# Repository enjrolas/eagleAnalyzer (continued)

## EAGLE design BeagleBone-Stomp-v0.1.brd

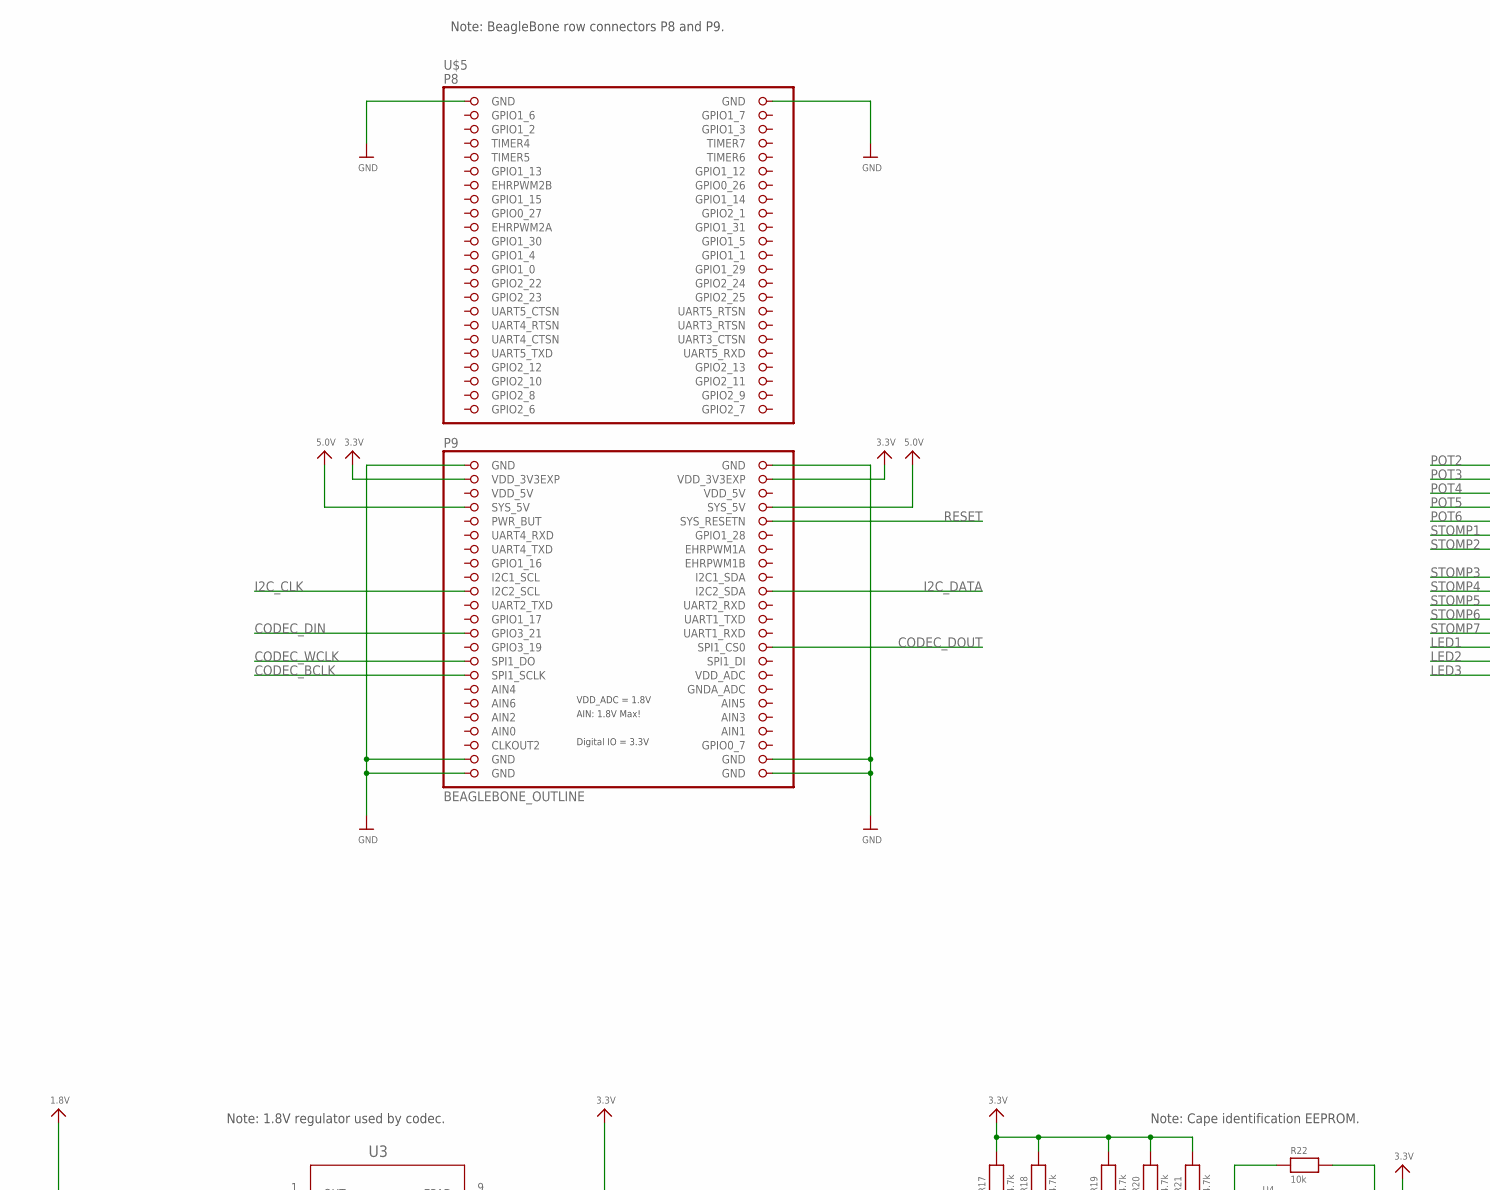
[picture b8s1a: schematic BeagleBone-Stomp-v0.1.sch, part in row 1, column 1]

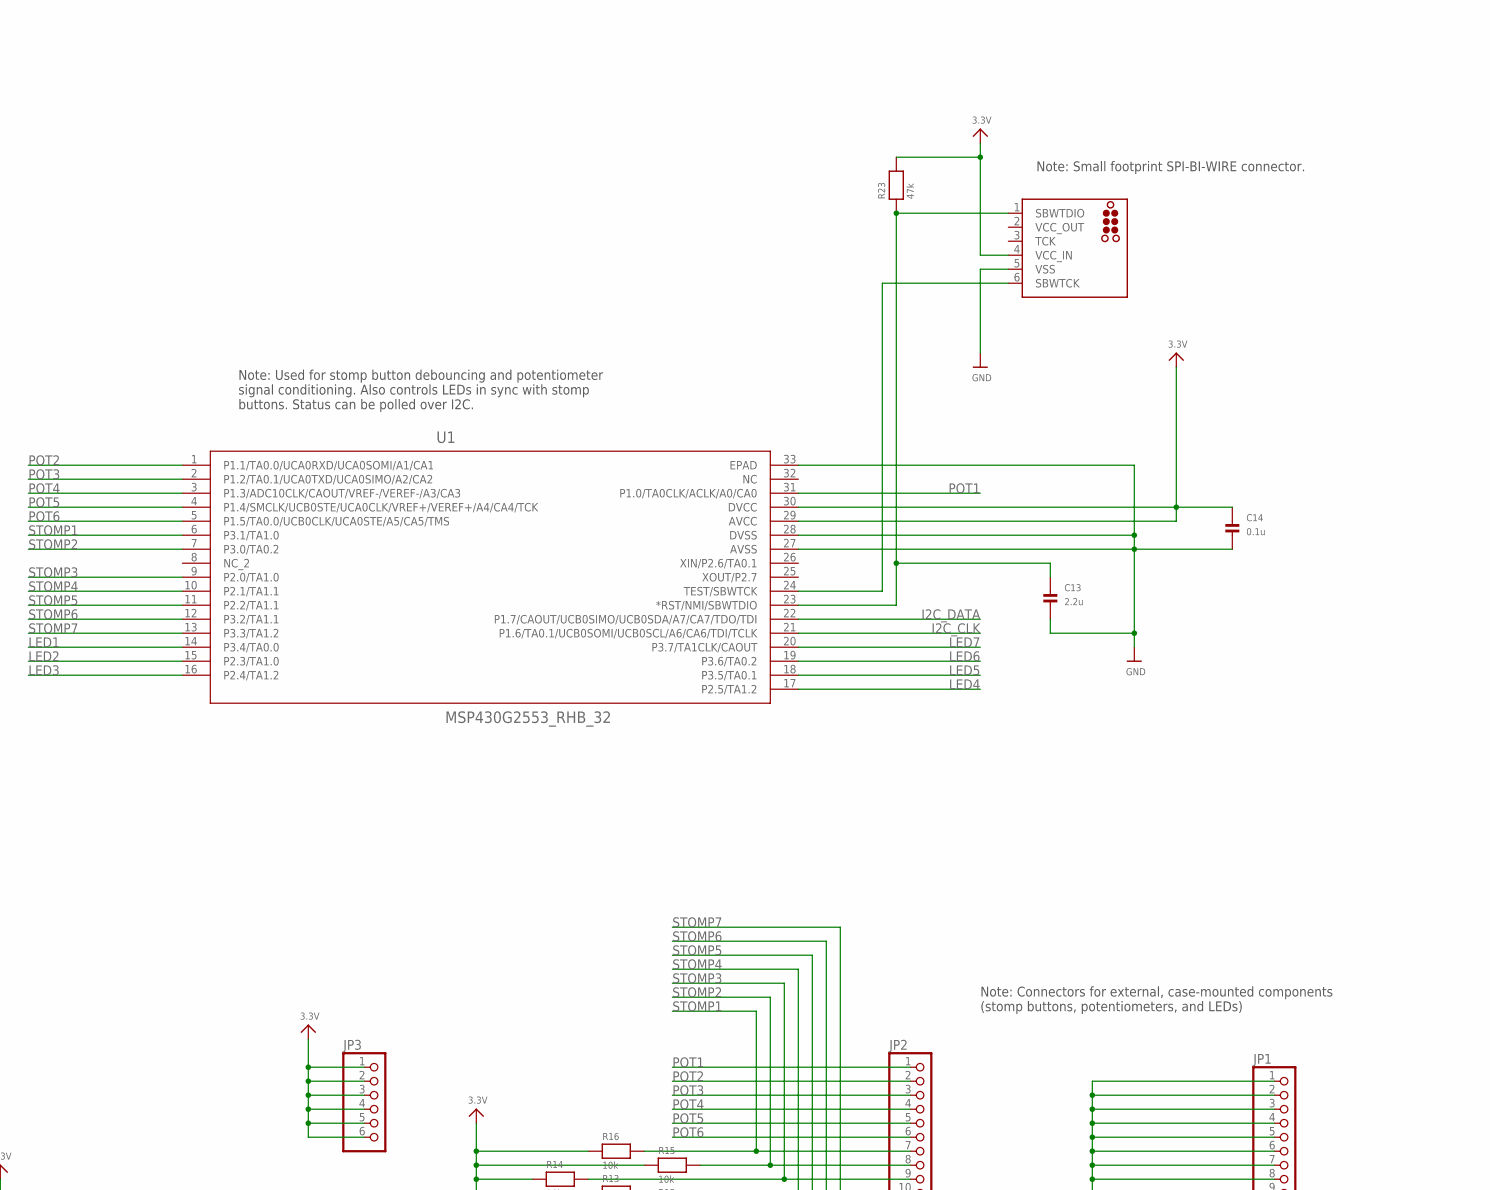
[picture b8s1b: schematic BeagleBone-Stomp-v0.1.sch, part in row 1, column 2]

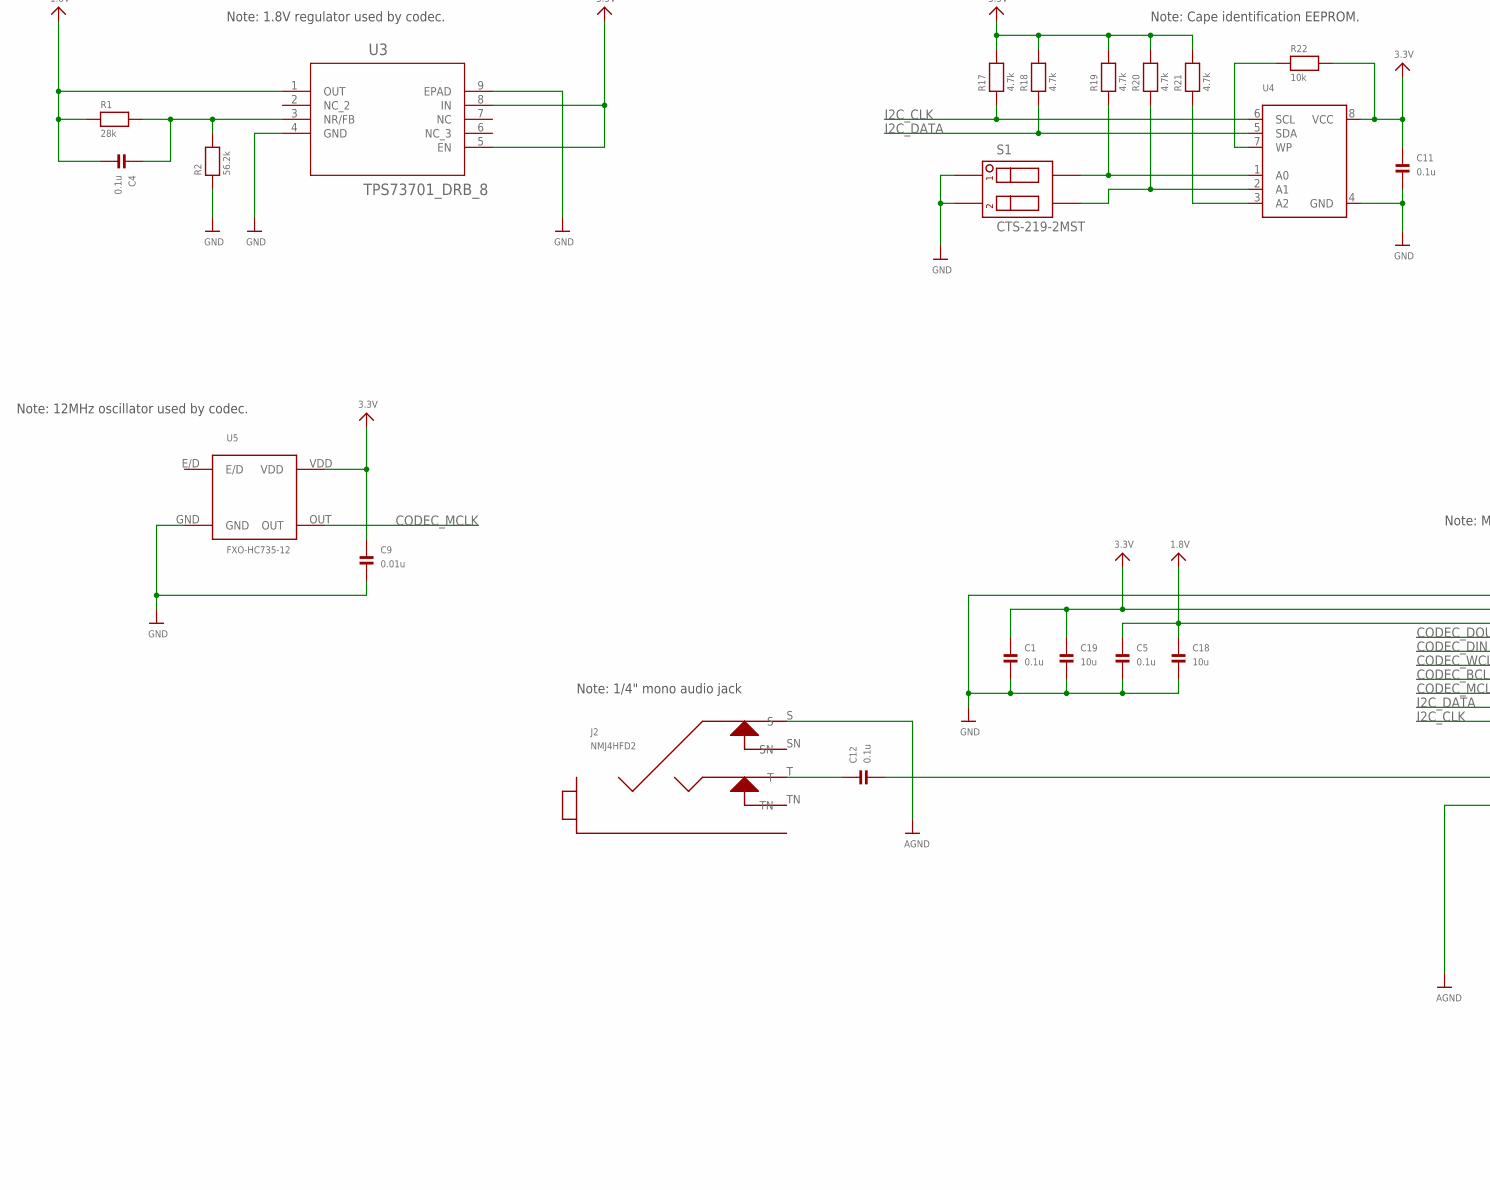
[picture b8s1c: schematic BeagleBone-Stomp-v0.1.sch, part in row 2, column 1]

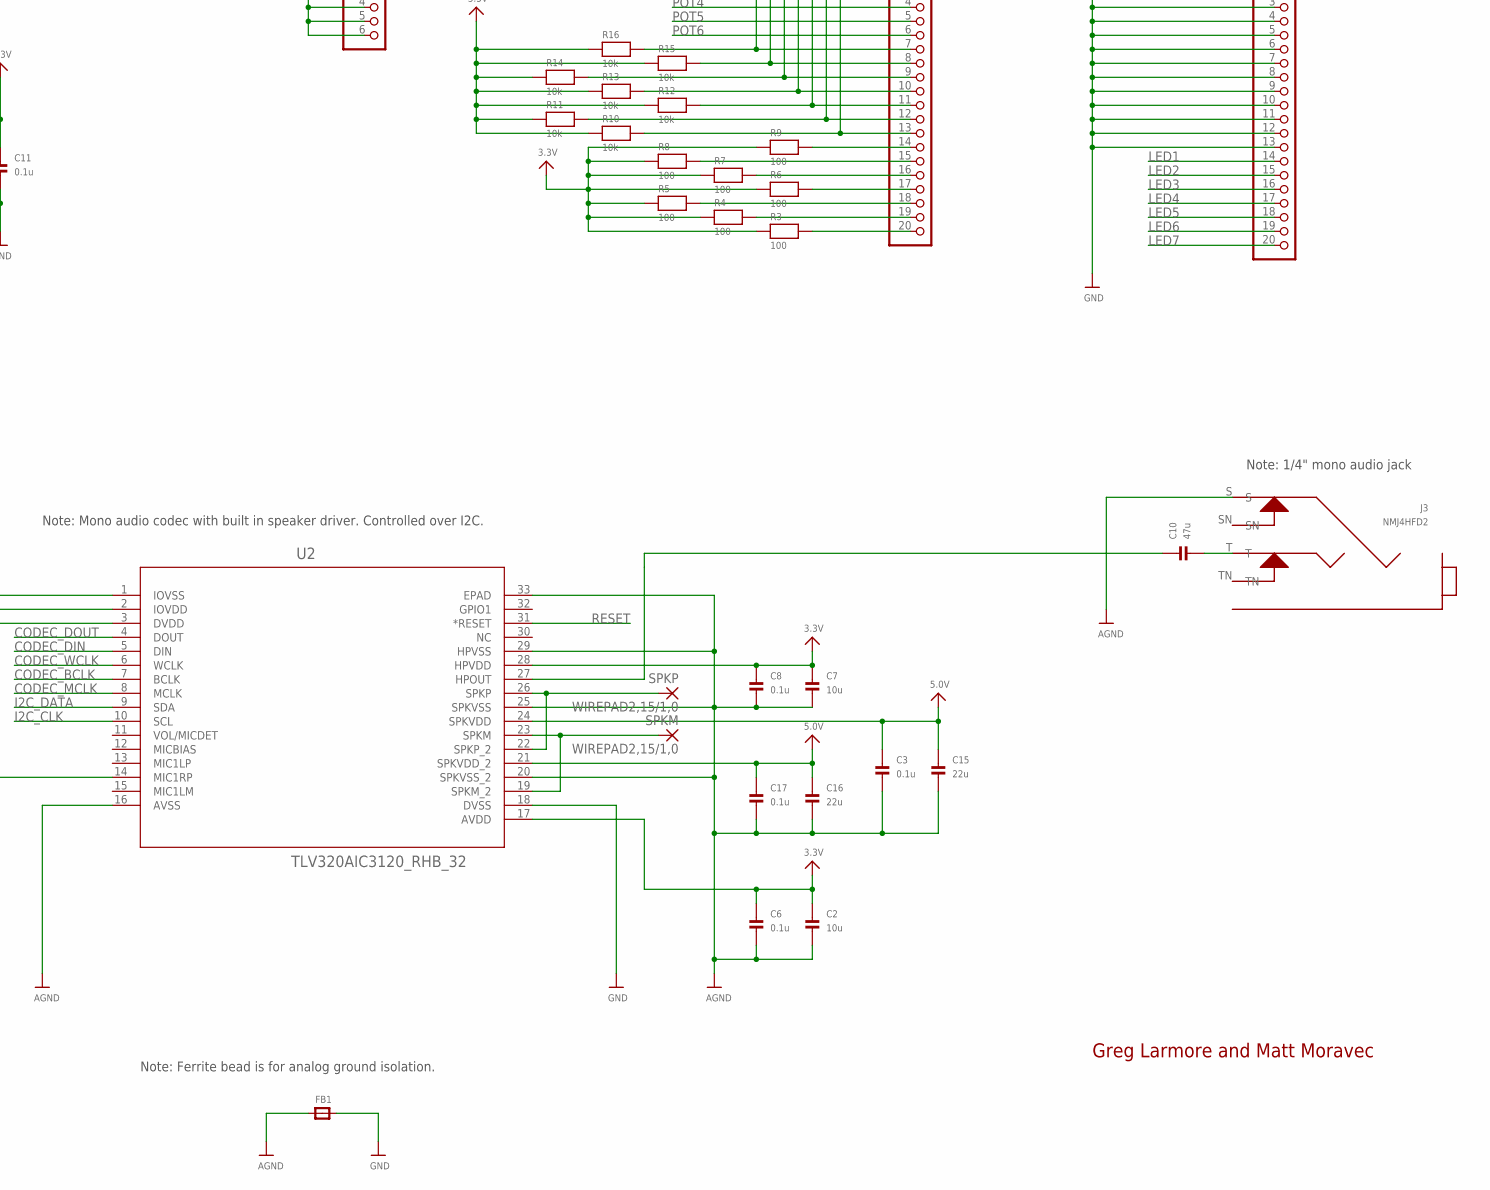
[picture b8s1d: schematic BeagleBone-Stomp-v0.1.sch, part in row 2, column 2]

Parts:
C1, C3, C4, C5, C6, C8, C11, C12, C14, C17: 0.1u; 0402
C2, C7, C18, C19: 10u; 0805
C9: 0.01u; 0402
C10: 47u; 0805
C13: 2.2u; 0402
C15, C16: 22u; 0805
FB1: FERRITE_0402; _0402
J1: TC2030-MCP
J2, J3: NMJ4HFD2
JP1, JP2: HEADER-1X20ROUND; 1X20_ROUND
JP3: HEADER-1X6ROUND; 1X06_ROUND
R1: 28k; 0402
R2: 56.2k; 0402
R3, R4, R5, R6, R7, R8, R9: 100; 0402
R10, R11, R12, R13, R14, R15, R16, R22: 10k; 0402
R17, R18, R19, R20, R21: 4.7k; 0402
R23: 47k; 0402
S1: CTS-219-2MST
SPKM: WIREPAD2,15/1,0; 2,15/1,0
SPKP: WIREPAD2,15/1,0; 2,15/1,0
U1: MSP430G2553_RHB_32; RHB32_3P45X3P45
U2: TLV320AIC3120_RHB_32; RHB32_3P45X3P45
U3: TPS73701_DRB_8; DRB8_1P75X1P5
U4: EEPROM_I2C_SOIC8_GENERIC; SOIC8_150MIL
U5: FXO-HC735-12
U$5: BEAGLEBONE_OUTLINE; BEAGLEBONE_SHIELD

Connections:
1.8V: C4.2, C5.1, C18.1, R1.1, U2.3 (DVDD), U3.1 (OUT)
3.3V: C1.1, C2.1, C6.1, C7.1, C8.1, C9.1, C11.1, C14.1, C19.1, J1.4 (VCC_IN), JP3.1, JP3.2, JP3.3, JP3.4, JP3.5, JP3.6, R3.1, R4.1, R5.1, R6.1, R7.1, R8.1, R9.1, R10.1, R11.1, R12.1, R13.1, R14.1, R15.1, R16.1, R17.2, R18.2, R19.2, R20.2, R21.2, R22.2, R23.2, U1.29 (AVCC), U1.30 (DVCC), U2.2 (IOVDD), U2.17 (AVDD), U2.28 (HPVDD), U3.5 (EN), U3.8 (IN), U4.8 (VCC), U5.VDD, U$5.49 (VDD_3V3EXP), U$5.50 (VDD_3V3EXP)
5.0V: C3.1, C15.1, C16.1, C17.1, U2.21 (SPKVDD_2), U2.24 (SPKVDD), U$5.53 (SYS_5V), U$5.54 (SYS_5V)
AGND: C2.2, C3.2, C6.2, C7.2, C8.2, C15.2, C16.2, C17.2, FB1.1, J2.S, J3.S, U2.16 (AVSS), U2.20 (SPKVSS_2), U2.25 (SPKVSS), U2.29 (HPVSS), U2.33 (EPAD)
CODEC_BCLK: U2.7 (BCLK), U$5.77 (SPI1_SCLK)
CODEC_DIN: U2.5 (DIN), U$5.71 (GPIO3_21)
CODEC_DOUT: U2.4 (DOUT), U$5.74 (SPI1_CS0)
CODEC_MCLK: U2.8 (MCLK), U5.OUT
CODEC_WCLK: U2.6 (WCLK), U$5.75 (SPI1_DO)
GND: C1.2, C5.2, C9.2, C11.2, C13.2, C14.2, C18.2, C19.2, FB1.2, J1.5 (VSS), JP1.1, JP1.2, JP1.3, JP1.4, JP1.5, JP1.6, JP1.7, JP1.8, JP1.9, JP1.10, JP1.11, JP1.12, JP1.13, R2.1, S1.P$1, S1.P$2, U1.27 (AVSS), U1.28 (DVSS), U1.33 (EPAD), U2.1 (IOVSS), U2.18 (DVSS), U3.4 (GND), U3.9 (EPAD), U4.4 (GND), U5.GND, U$5.1 (GND), U$5.2 (GND), U$5.47 (GND), U$5.48 (GND), U$5.89 (GND), U$5.90 (GND), U$5.91 (GND), U$5.92 (GND)
GNDA_ADC: U$5.80 (GNDA_ADC)
I2C_CLK: R17.1, U1.21 (P1.6/TA0.1/UCB0SOMI/UCB0SCL/A6/CA6/TDI/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), U2.10 (SCL), U4.6 (SCL), U$5.65 (I2C2_SCL)
I2C_DATA: R18.1, U1.22 (P1.7/CAOUT/UCB0SIMO/UCB0SDA/A7/CA7/TDO/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), U2.9 (SDA), U4.5 (SDA), U$5.66 (I2C2_SDA)
LED1: JP1.14, U1.14 (P3.4/TA0.0)
LED2: JP1.15, U1.15 (P2.3/TA1.0)
LED3: JP1.16, U1.16 (P2.4/TA1.2)
LED4: JP1.17, U1.17 (P2.5/TA1.2)
LED5: JP1.18, U1.18 (P3.5/TA0.1)
LED6: JP1.19, U1.19 (P3.6/TA0.2)
LED7: JP1.20, U1.20 (P3.7/TA1CLK/CAOUT)
unnamed: C4.1, R1.2, R2.2, U3.3 (NR/FB)
unnamed: SPKM.1, U2.19 (SPKM_2), U2.23 (SPKM)
unnamed: SPKP.1, U2.22 (SPKP_2), U2.26 (SPKP)
unnamed: R19.1, S1.P$4, U4.1 (A0)
unnamed: C10.2, J3.T
unnamed: JP2.20, R3.2
unnamed: C10.1, U2.27 (HPOUT)
unnamed: C12.1, J2.T
unnamed: C12.2, U2.14 (MIC1RP)
unnamed: R20.1, S1.P$3, U4.2 (A1)
unnamed: R21.1, U4.3 (A2)
unnamed: JP2.14, R9.2
unnamed: JP2.15, R8.2
unnamed: JP2.16, R7.2
unnamed: JP2.17, R6.2
unnamed: R22.1, U4.7 (WP)
unnamed: JP2.18, R5.2
unnamed: JP2.19, R4.2
unnamed: J1.6 (SBWTCK), U1.24 (TEST/SBWTCK)
unnamed: C13.1, J1.1 (SBWTDIO), R23.1, U1.23 (*RST/NMI/SBWTDIO)
POT1: JP2.1, U1.31 (P1.0/TA0CLK/ACLK/A0/CA0)
POT2: JP2.2, U1.1 (P1.1/TA0.0/UCA0RXD/UCA0SOMI/A1/CA1)
POT3: JP2.3, U1.2 (P1.2/TA0.1/UCA0TXD/UCA0SIMO/A2/CA2)
POT4: JP2.4, U1.3 (P1.3/ADC10CLK/CAOUT/VREF-/VEREF-/A3/CA3)
POT5: JP2.5, U1.4 (P1.4/SMCLK/UCB0STE/UCA0CLK/VREF+/VEREF+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)
POT6: JP2.6, U1.5 (P1.5/TA0.0/UCB0CLK/UCA0STE/A5/CA5/TMS)
RESET: U2.31 (*RESET), U$5.56 (SYS_RESETN)
STOMP1: JP2.7, R16.2, U1.6 (P3.1/TA1.0)
STOMP2: JP2.8, R15.2, U1.7 (P3.0/TA0.2)
STOMP3: JP2.9, R14.2, U1.9 (P2.0/TA1.0)
STOMP4: JP2.10, R13.2, U1.10 (P2.1/TA1.1)
STOMP5: JP2.11, R12.2, U1.11 (P2.2/TA1.1)
STOMP6: JP2.12, R11.2, U1.12 (P3.2/TA1.1)
STOMP7: JP2.13, R10.2, U1.13 (P3.3/TA1.2)
TCK: J1.3 (TCK)
VCC_OUT: J1.2 (VCC_OUT)
VDD_5V: U$5.51 (VDD_5V), U$5.52 (VDD_5V)
VDD_ADC: U$5.78 (VDD_ADC)

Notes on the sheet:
Note: Used for stomp button debouncing and potentiometer signal conditioning. Also controls LEDs in sync with stomp buttons. Status can be polled over I2C.
Note: Small footprint SPI-BI-WIRE connector.
Note: Connectors for external, case-mounted components (stomp buttons, potentiometers, and LEDs)
Note: Mono audio codec with built in speaker driver. Controlled over I2C.
Note: Ferrite bead is for analog ground isolation.
Note: 12MHz oscillator used by codec.
Note: 1.8V regulator used by codec.
Note: Cape identification EEPROM.
Note: BeagleBone row connectors P8 and P9.
Note: 1/4" mono audio jack
Greg Larmore and Matt Moravec

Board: 2 copper layers, 58 parts (0 on the bottom side), 54 nets, no tracks yet.
